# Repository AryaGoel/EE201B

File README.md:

# EE201
# EE201 Lab B
## Made by Arya Goel

Welcome to EE 201, this is *Arya Goel*, the creator of this file and repository.

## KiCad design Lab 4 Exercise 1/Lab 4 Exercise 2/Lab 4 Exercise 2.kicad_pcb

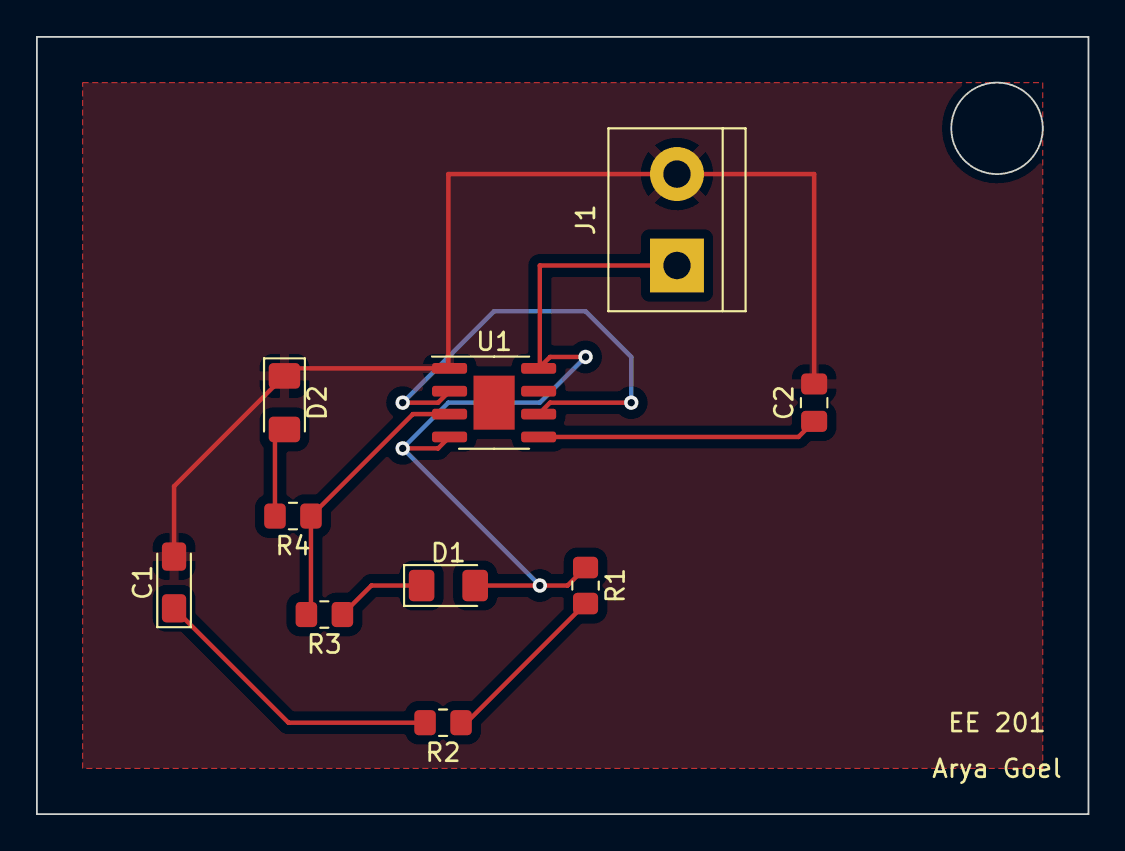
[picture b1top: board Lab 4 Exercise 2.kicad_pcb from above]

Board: 2 copper layers, 58.4 x 43.2 mm, 10 parts (0 on the bottom side), 9 nets.

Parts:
C1: 10 mu F; CP_EIA-3216-18_Kemet-A_Pad1.58x1.35mm_HandSolder
C2: 0.01 mu F; C_0805_2012Metric_Pad1.18x1.45mm_HandSolder
D1, D2: LED; LED_1206_3216Metric_Pad1.42x1.75mm_HandSolder
J1: TerminalBlock_bornier-2_P5.08mm
R1, R3, R4: 1K; R_0805_2012Metric_Pad1.20x1.40mm_HandSolder
R2: 10K; R_0805_2012Metric_Pad1.20x1.40mm_HandSolder
U1: NE555D; SOIC-8-1EP_3.9x4.9mm_P1.27mm_EP2.29x3mm

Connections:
+9V: D1.2 (A), J1.1, R1.1, U1.4 (R), U1.8 (VCC)
/pin_2: U1.2 (TR), U1.6 (THR)
/pin_3: R3.2, R4.1, U1.3 (Q)
GND: C1.2, C2.2, D2.1 (K), J1.2, U1.1 (GND)
unnamed: C1.1, R2.2
unnamed: C2.1, U1.5 (CV)
unnamed: D1.1 (K), R3.1
unnamed: D2.2 (A), R4.2
unnamed: R1.2, R2.1

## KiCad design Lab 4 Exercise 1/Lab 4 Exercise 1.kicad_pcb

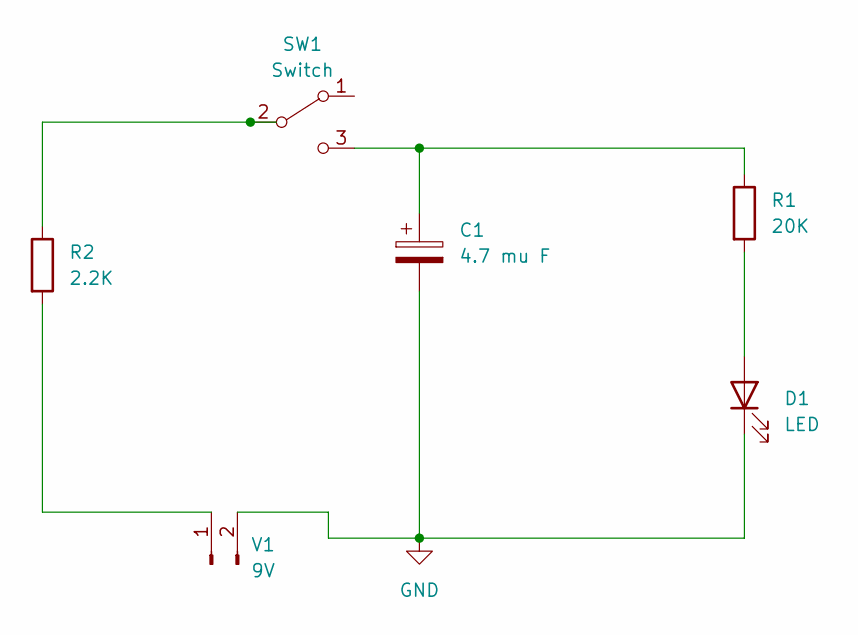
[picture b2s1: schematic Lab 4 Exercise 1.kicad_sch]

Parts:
C1: 4.7 mu F; C_Radial_D5.0mm_H5.0mm_P2.00mm
D1: LED; LED_D5.0mm
R1: 20K; R_Axial_DIN0516_L15.5mm_D5.0mm_P20.32mm_Horizontal
R2: 2.2K; R_Axial_DIN0516_L15.5mm_D5.0mm_P20.32mm_Horizontal
SW1: Switch; SW_E-Switch_EG1224_SPDT_Angled
V1: 9V; JST_PH_B2B-PH-K_1x02_P2.00mm_Vertical

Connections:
GND: C1.2, D1.1 (K), V1.2
unnamed: C1.1, R1.1, SW1.3 (C)
unnamed: D1.2 (A), R1.2
unnamed: R2.1, SW1.2 (B)
unnamed: R2.2, V1.1

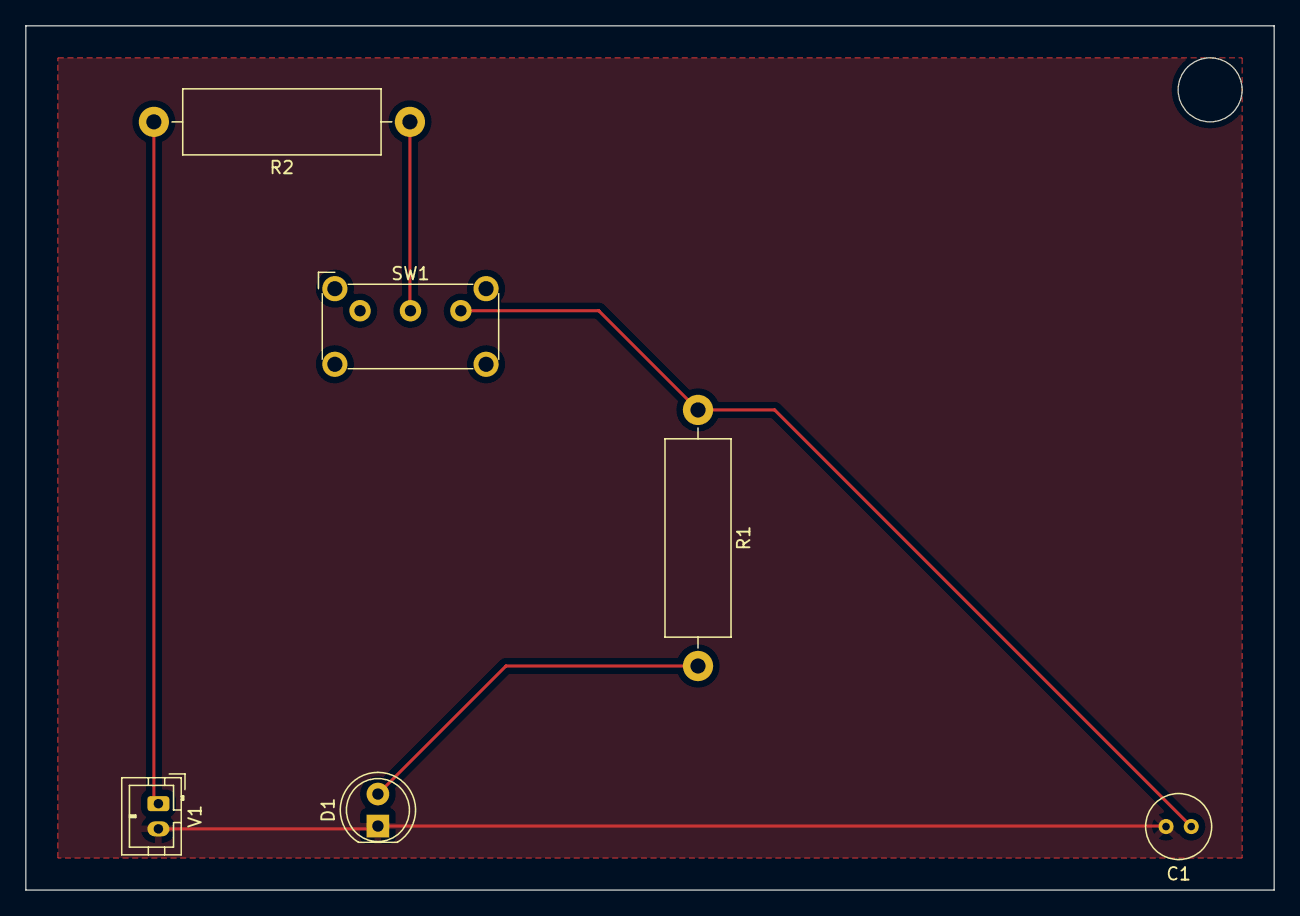
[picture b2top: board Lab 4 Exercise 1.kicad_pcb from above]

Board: 2 copper layers, 99.1 x 68.6 mm, 6 parts (0 on the bottom side), 5 nets.

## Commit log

2023-01-31 Add changes
2023-01-31 change
2023-01-31 Lab 4 Added
2023-02-02 Lab 5 Added
2023-02-09 Lab 6 added
2023-02-16 Lab 7 Added
2023-03-09 Lab 8 Added
